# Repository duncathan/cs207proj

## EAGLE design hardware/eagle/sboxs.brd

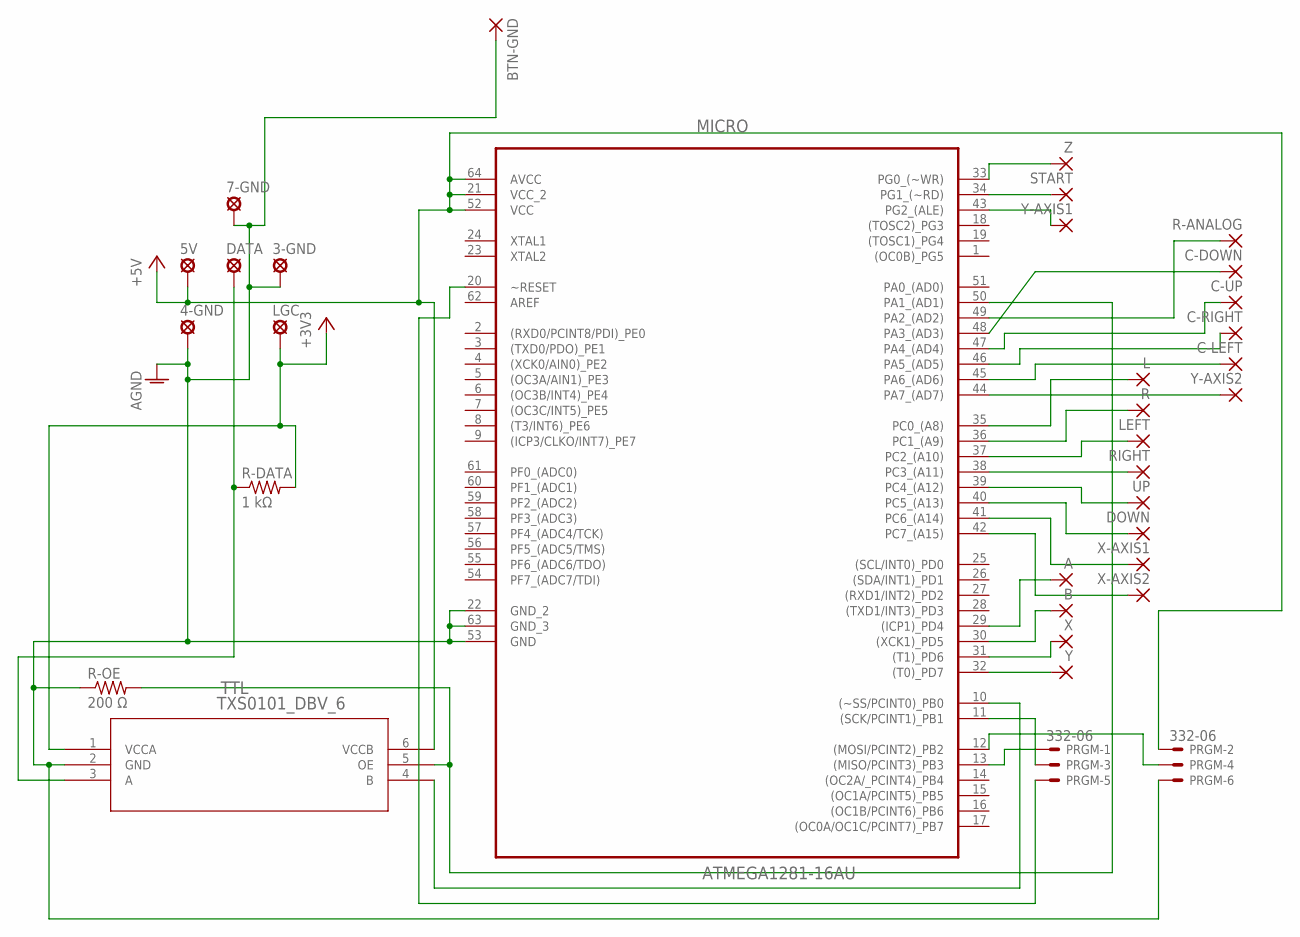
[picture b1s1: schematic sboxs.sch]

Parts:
3-GND, 4-GND, 5V, 7-GND: LSP10
A: 1,6/0,8
B: 1,6/0,8
BTN-GND: 1,6/0,8
C-DOWN: 1,6/0,8
C-LEFT: 1,6/0,8
C-RIGHT: 1,6/0,8
C-UP: 1,6/0,8
DATA: LSP10
DOWN: 1,6/0,8
L: 1,6/0,8
LEFT: 1,6/0,8
LGC: LSP10
MICRO: ATMEGA1281-16AU; QFP80P1600X1600X120-64N
PRGM: 332-06
R: 1,6/0,8
R-ANALOG: 1,6/0,8
R-DATA: 1 kΩ; 0207/12
R-OE: 200 Ω; 0207/12
RIGHT: 1,6/0,8
START: 1,6/0,8
TTL: TXS0101_DBV_6; DBV6
UP: 1,6/0,8
X: 1,6/0,8
X-AXIS1, X-AXIS2: 1,6/0,8
Y: 1,6/0,8
Y-AXIS1, Y-AXIS2: 1,6/0,8
Z: 1,6/0,8

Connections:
+3V3: LGC.MP, R-DATA.2, TTL.1 (VCCA)
+5V: 5V.MP, MICRO.21 (VCC_2), MICRO.52 (VCC), MICRO.64 (AVCC), PRGM.2, TTL.6 (VCCB)
AGND: 3-GND.MP, 4-GND.MP, 7-GND.MP, BTN-GND.1, MICRO.22 (GND_2), MICRO.53 (GND), MICRO.63 (GND_3), PRGM.6, R-OE.1, TTL.2 (GND)
unnamed: MICRO.32 ((T0)_PD7), Y.1
unnamed: MICRO.31 ((T1)_PD6), X.1
unnamed: B.1, MICRO.30 ((XCK1)_PD5)
unnamed: A.1, MICRO.29 ((ICP1)_PD4)
unnamed: MICRO.33 (PG0_(~WR)), Z.1
unnamed: MICRO.34 (PG1_(~RD)), START.1
unnamed: L.1, MICRO.35 (PC0_(A8))
unnamed: MICRO.36 (PC1_(A9)), R.1
unnamed: LEFT.1, MICRO.37 (PC2_(A10))
unnamed: MICRO.38 (PC3_(A11)), RIGHT.1
unnamed: MICRO.39 (PC4_(A12)), UP.1
unnamed: DOWN.1, MICRO.40 (PC5_(A13))
unnamed: MICRO.41 (PC6_(A14)), X-AXIS1.1
unnamed: MICRO.42 (PC7_(A15)), X-AXIS2.1
unnamed: MICRO.44 (PA7_(AD7)), Y-AXIS2.1
unnamed: C-LEFT.1, MICRO.45 (PA6_(AD6))
unnamed: C-RIGHT.1, MICRO.46 (PA5_(AD5))
unnamed: C-UP.1, MICRO.47 (PA4_(AD4))
unnamed: C-DOWN.1, MICRO.48 (PA3_(AD3))
unnamed: MICRO.49 (PA2_(AD2)), R-ANALOG.1
unnamed: MICRO.13 ((MISO/PCINT3)_PB3), PRGM.1
unnamed: MICRO.12 ((MOSI/PCINT2)_PB2), PRGM.4
unnamed: MICRO.11 ((SCK/PCINT1)_PB1), PRGM.3
unnamed: MICRO.43 (PG2_(ALE)), Y-AXIS1.1
unnamed: MICRO.20 (~RESET), PRGM.5
unnamed: DATA.MP, R-DATA.1, TTL.3 (A)
unnamed: MICRO.10 ((~SS/PCINT0)_PB0), TTL.4 (B)
unnamed: MICRO.50 (PA1_(AD1)), R-OE.2, TTL.5 (OE)

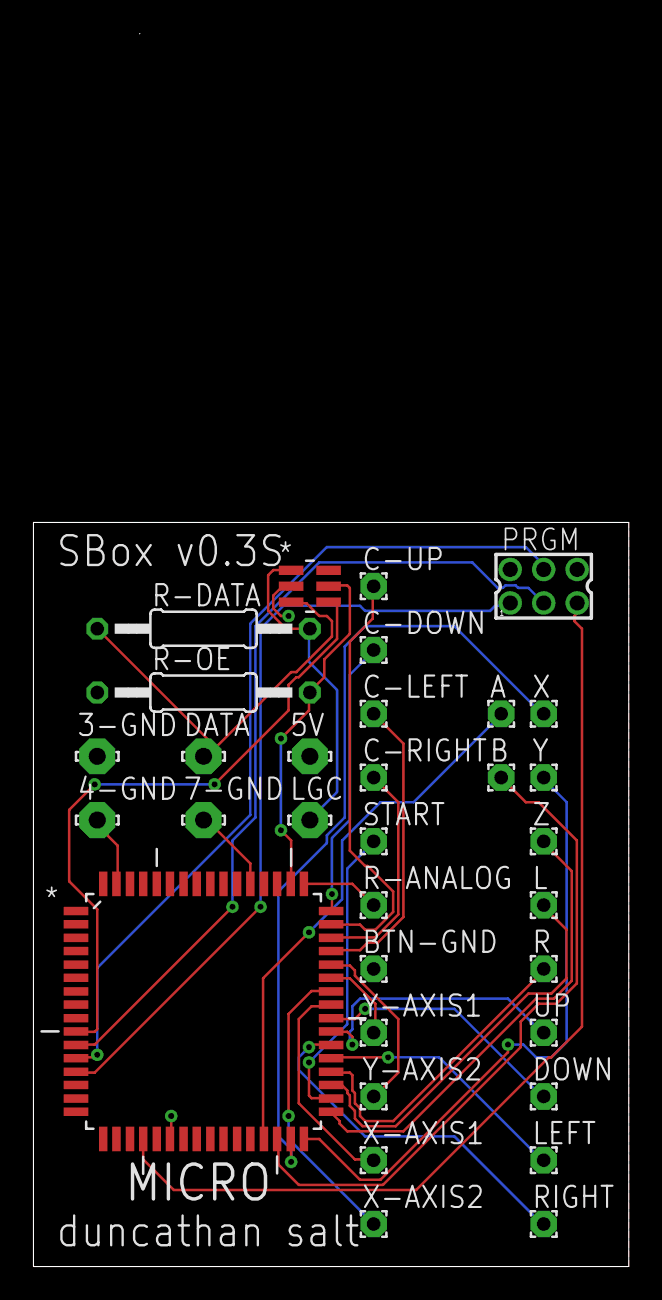
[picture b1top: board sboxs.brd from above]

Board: 2 copper layers, 35.6 x 73.7 mm, 33 parts (0 on the bottom side), 31 nets.

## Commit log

2018-02-15 add license
2018-02-16 directory initialization
2018-03-04 first attempt at interfacing with the console
    just mashes the start button for now
    also included several defines for pinout/constants/etc
2018-03-04 improved debugging; removes artificial delay unless necessary
2018-03-04 adds the functionality needed to function as a proper HMI
2018-03-08 add eagle schematic v0.2, large pcb diagram v0.2, small pcb diagram v0.3
2018-03-08 update to small pcb v0.2 and minor changes to overall schematic
2018-03-08 small pcb v0.3
2018-03-17 fix compile errors and additional minor improvements
2018-03-17 adds support for axe-style shield drops
